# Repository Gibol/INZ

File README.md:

INZ
===

PCM-2 and ADA-2 software and hardware

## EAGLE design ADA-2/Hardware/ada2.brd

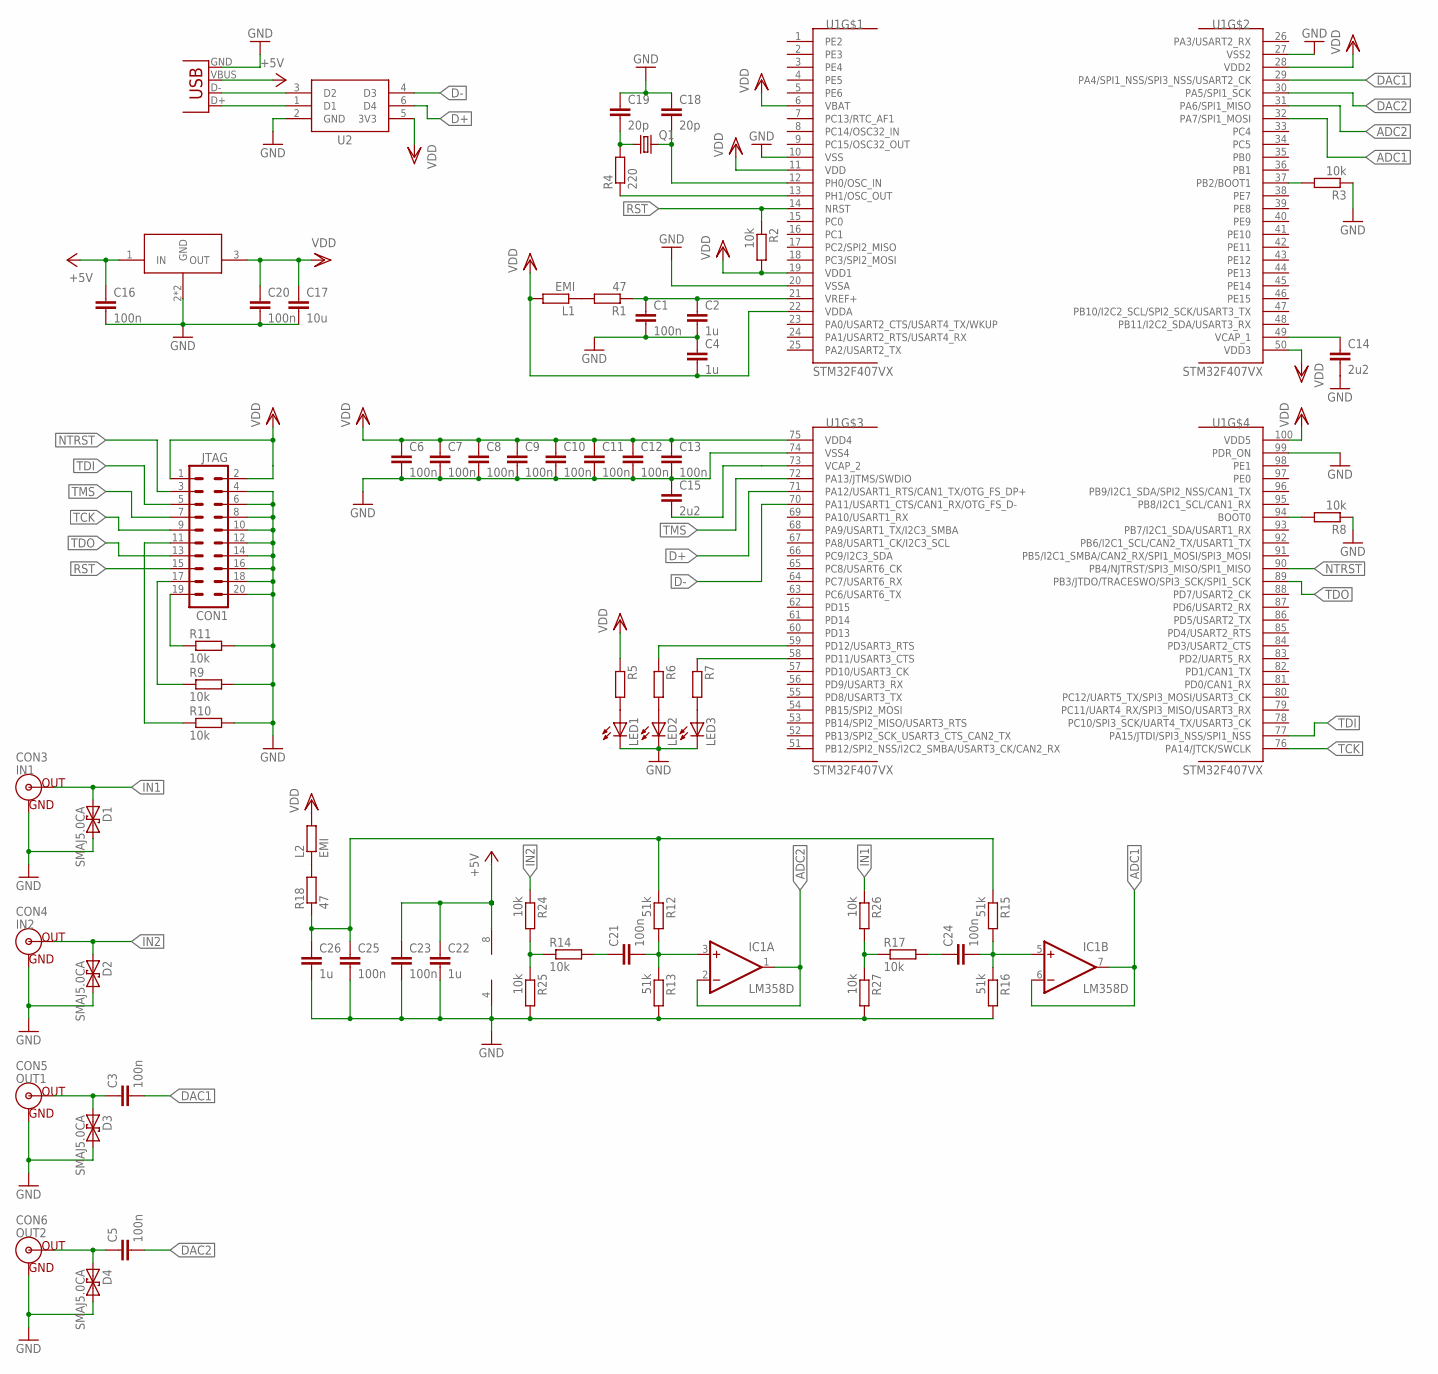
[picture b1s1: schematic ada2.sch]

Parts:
C1, C3, C5, C6, C7, C8, C9, C10, C11, C12, C13, C16, C20, C21, C23, C24, C25: 100n; C0603K
C2, C4, C22, C26: 1u; C0603K
C14, C15: 2u2; C0603K
C17: 10u; C0603K
C18, C19: 20p; C0603K
CON1: JTAG; ML20
CON2: USB-B; USB-B-PTH
CON3: IN1; BNC
CON4: IN2; BNC
CON5: OUT1; BNC
CON6: OUT2; BNC
D1, D2, D3, D4: SMAJ5.0CA; SMA-DIODE
IC1: LM358D; SO08
L1, L2: EMI; R0603
LED1, LED2, LED3: KONTROLKA_LED
Q1: CRYSTALHC49UP; HC49UP
R1, R18: 47; R0603
R2, R3, R8, R9, R10, R11, R14, R17, R24, R25, R26, R27: 10k; R0603
R4: 220; R0603
R5, R6, R7: R-EU_R0603; R0603
R12, R13, R15, R16: 51k; R0603
U1: STM32F407VX; LQFP100
U2: USBUF01W6; SOT363
U3: MCP1703; SOT223

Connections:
+5V: C16.1, C22.1, C23.1, CON2.VBUS, IC1.8 (V+), U3.1 (IN)
ADC1: IC1.6 (-IN), IC1.7 (OUT), U1.32 (PA7/SPI1_MOSI)
ADC2: IC1.1 (OUT), IC1.2 (-IN), U1.31 (PA6/SPI1_MISO)
D+: U1.71 (PA12/USART1_RTS/CAN1_TX/OTG_FS_DP+), U2.6 (D4)
D-: U1.70 (PA11/USART1_CTS/CAN1_RX/OTG_FS_D-), U2.4 (D3)
DAC1: C3.2, U1.29 (PA4/SPI1_NSS/SPI3_NSS/USART2_CK)
DAC2: C5.2, U1.30 (PA5/SPI1_SCK)
GND: C1.2, C2.2, C4.1, C6.2, C7.2, C8.2, C9.2, C10.2, C11.2, C12.2, C13.2, C14.2, C15.1, C16.2, C17.2, C18.1, C19.1, C20.2, C22.2, C23.2, C25.2, C26.2, CON1.4, CON1.6, CON1.8, CON1.10, CON1.12, CON1.14, CON1.16, CON1.18, CON1.20, CON2.GND, CON3.GND, CON4.GND, CON5.GND, CON6.GND, D1.C (2), D2.C (2), D3.C (2), D4.C (2), IC1.4 (V-), LED1.K (C), LED2.K (C), LED3.K (C), R3.1, R8.1, R9.2, R10.2, R11.2, R13.2, R16.2, R25.2, R27.2, U1.10 (VSS), U1.20 (VSSA), U1.27 (VSS2), U1.74 (VSS4), U1.99 (PDR_ON), U2.2 (GND), U3.2 (GND), U3.2@2 (GND)
IN1: CON3.S (OUT), D1.A (1), R26.1
IN2: CON4.S (OUT), D2.A (1), R24.1
unnamed: L1.1, R1.2
unnamed: C21.1, R14.2
unnamed: CON2.D-, U2.3 (D2)
unnamed: CON2.D+, U2.1 (D1)
unnamed: R4.1, U1.13 (PH1/OSC_OUT)
unnamed: C19.2, Q1.1, R4.2
unnamed: C15.2, U1.73 (VCAP_2)
unnamed: C14.1, U1.49 (VCAP_1)
unnamed: C3.1, CON5.S (OUT), D3.A (1)
unnamed: R3.2, U1.37 (PB2/BOOT1)
unnamed: C18.2, Q1.2, U1.12 (PH0/OSC_IN)
unnamed: LED1.A, R5.2
unnamed: LED2.A, R6.2
unnamed: LED3.A, R7.2
unnamed: R7.1, U1.58 (PD11/USART3_CTS)
unnamed: R6.1, U1.59 (PD12/USART3_RTS)
unnamed: C5.1, CON6.S (OUT), D4.A (1)
unnamed: CON1.19, R11.1
unnamed: CON1.17, R9.1
unnamed: CON1.11, R10.1
unnamed: R14.1, R24.2, R25.1
unnamed: L2.1, R18.2
unnamed: C21.2, IC1.3 (+IN), R12.2, R13.1
unnamed: C24.1, R17.2
unnamed: C25.1, C26.1, R12.1, R15.1, R18.1
unnamed: R17.1, R26.2, R27.1
unnamed: R8.2, U1.94 (BOOT0)
unnamed: C24.2, IC1.5 (+IN), R15.2, R16.1
NTRST: CON1.3, U1.90 (PB4/NJTRST/SPI3_MISO/SPI1_MISO)
RST: CON1.15, R2.1, U1.14 (NRST)
TCK: CON1.9, U1.76 (PA14/JTCK/SWCLK)
TDI: CON1.5, U1.77 (PA15/JTDI/SPI3_NSS/SPI1_NSS)
TDO: CON1.13, U1.89 (PB3/JTDO/TRACESWO/SPI3_SCK/SPI1_SCK)
TMS: CON1.7, U1.72 (PA13/JTMS/SWDIO)
VDD: C4.2, C6.1, C7.1, C8.1, C9.1, C10.1, C11.1, C12.1, C13.1, C17.1, C20.1, CON1.1, CON1.2, L1.2, L2.2, R2.2, R5.1, U1.6 (VBAT), U1.11 (VDD), U1.19 (VDD1), U1.22 (VDDA), U1.28 (VDD2), U1.50 (VDD3), U1.75 (VDD4), U1.100 (VDD5), U2.5 (3V3), U3.3 (OUT)
VREF: C1.1, C2.1, R1.1, U1.21 (VREF+)

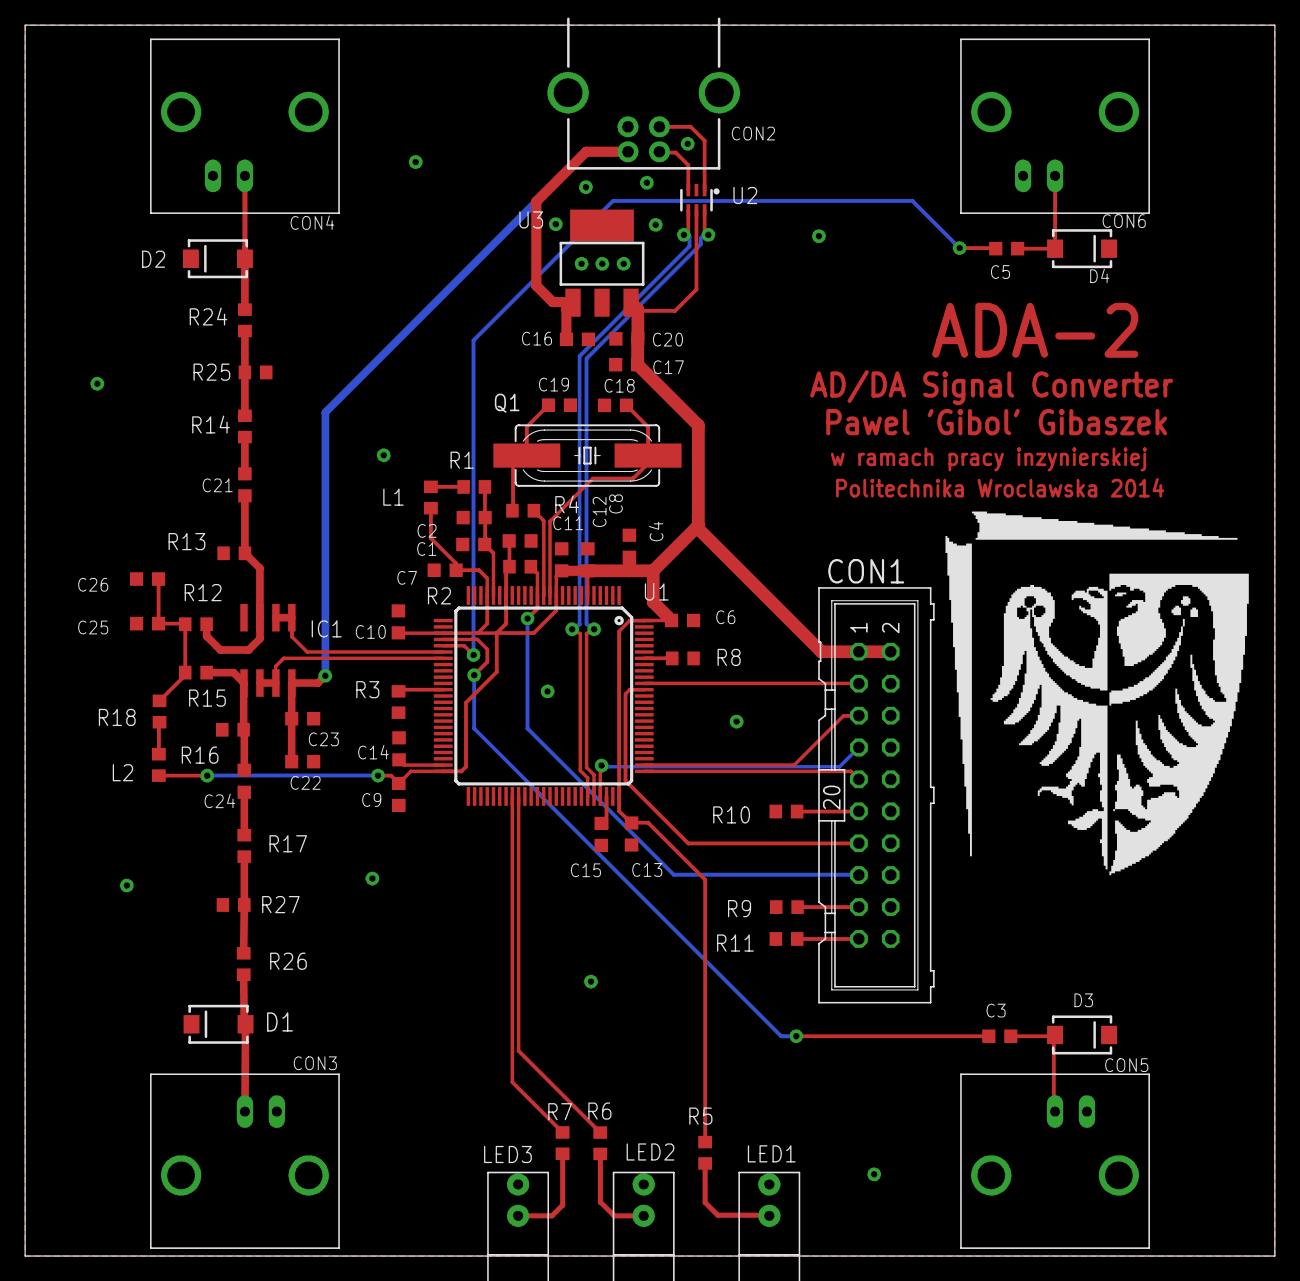
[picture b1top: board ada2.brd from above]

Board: 2 copper layers, 99.5 x 98.0 mm, 68 parts (0 on the bottom side), 46 nets.

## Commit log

2014-12-23 fixed some bugs in usb transmission handling
2014-12-29 Work in progress :)
2014-12-29 Fixed some communication issues, sending configuration is working. Most part of the GUI is missing and only 12 bit wordLen with no compression is working for now.
2014-12-30 TODO: implement g711 functions; build final gui.
2015-01-05 Version 1.0 (for paper). Missing didactics.
2015-01-08 Fixed bug in TIM6_DAC_IRQ_Handler, minor changes in data transmission, fixed trigger issue, fixed graph not being updated when thre is no new data.
2015-01-11 Version 1.1 Added analog compression, more word lenghts, polish translation, etc.
2015-01-11 missing from previous commit...
2015-01-20 Release v1.1 (after testing and acceptance)

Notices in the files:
parts and their libraries:
SparkFun-Connectors: Licensing: Creative Commons ShareAlike 4.0 International - https://creativecommons.org/licenses/by-sa/4.0
SparkFun: Licensing: CC v3.0 Share-Alike You are welcome to use this library for commercial purposes.
